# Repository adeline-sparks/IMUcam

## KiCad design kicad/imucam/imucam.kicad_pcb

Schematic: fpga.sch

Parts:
C1, C3, C5, C6, C7, C10, C11, C13, C16, C18, C20, C23, C25, C26, C27, C28, C29, C30, C31, C32, C33, C35, C37: 100nF; C_0402_1005Metric
C2, C8, C36: 1uF; C_0402_1005Metric
C4: 2.2uF; C_0402_1005Metric
C9, C12, C14, C15, C17, C19, C21, C22, C24, C34: 10uF; C_0603_1608Metric
D1: D_Schottky; D_0402_1005Metric
DONE1: RED; LED_0805_2012Metric
FB1, FB2, FB3, FB4, FB5: 120; L_0402_1005Metric
FPGA_LED1, FPGA_LED2, FPGA_LED3: RED; LED_0805_2012Metric
J1: JTAG; PinHeader_2x05_P1.27mm_Vertical
Q1, Q2, Q3, Q4: BSS214NW; SOT-323_SC-70
R1, R3, R5, R8, R11, R15: 10k; R_0402_1005Metric
R2, R4, R6, R9: 100; R_0402_1005Metric
R7, R12: 1k; R_0402_1005Metric
R10, R13, R14: 4.7k; R_0402_1005Metric
R16: 2.2k; R_0402_1005Metric
U1: TLV73310PDBVT; SOT-23-5
U2: LIFCL-17-xSG72; QFN-72-1EP_10x10mm_P0.5mm_EP6x6mm
U3: AT25SF081-SSHD-X; SOIC-8_3.9x4.9mm_P1.27mm
X1: ECS-2520MV-xxx-xx; Oscillator_SMD_ECS_2520MV-xxx-xx-4Pin_2.5x2.0mm

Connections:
+1V0: C1.1, C3.1, C5.1, C7.1, C8.1, C10.1, C12.1, C13.1, C17.1, C18.1, C24.1, C25.1, FB1.1, FB3.1, U1.5, U2.5 (VCC), U2.6 (VCC), U2.12 (VCC), U2.21 (VCC), U2.35 (VCC), U2.38 (VCC), U2.40 (VCC), U2.62 (VCC)
/FPGA/1V0A_PHY: C15.1, C16.1, C23.1, FB3.2, U2.70 (VCCDPHY0), U2.72 (VCCDPHY0)
/FPGA/1V0A_PLL: C4.1, C6.1, FB1.2, U2.63 (VCCPLLDPHY0)
/FPGA/1V8A: C30.1, C31.1, C32.1, C33.1, C34.1, FB4.2, U2.7 (VCCAUX), U2.17 (VCCAUXH5), U2.29 (VCCAUXH3), U2.47 (VCCAUX)
/FPGA/1V8A_PHY: C9.1, C11.1, FB2.2, U2.71 (VCCADPHY0)
/FPGA/FLASH_CS: R11.2, U2.56 (PT61A/MCSN), U3.1
/FPGA/FLASH_SCK: R12.1, U2.59 (PT59A/MCLK), U3.6
/FPGA/FLASH_SI: U2.57 (PT61B/MOSI), U3.5
/FPGA/FLASH_SO: U2.51 (PT63A/MISO), U3.2
/FPGA/JTAG_RESET: D1.2, J1.10, R15.2, U2.60 (PT57B/PROGRAMN)
/FPGA/JTAG_TCK: J1.4, R16.1, U2.41 (PR9A/TCK)
/FPGA/JTAG_TDI: J1.8, R10.2, U2.46 (PR5A/TDI)
/FPGA/JTAG_TDO: J1.6, R13.2, U2.45 (PR5B/TDO)
/FPGA/JTAG_TMS: J1.2, R14.2, U2.48 (PR3B/TMS)
/FPGA/LED1: Q1.1, R1.1, U2.9 (PB30A)
/FPGA/LED2: Q2.1, R3.1, U2.8 (PB30B)
/FPGA/LED3: Q3.1, R5.1, U2.37 (PB70B)
CAM_SLVS0_N: U2.34 (PB68B); also elsewhere on the board
CAM_SLVS0_P: U2.33 (PB68A); also elsewhere on the board
CAM_SLVS1_N: U2.31 (PB66B); also elsewhere on the board
CAM_SLVS1_P: U2.30 (PB66A); also elsewhere on the board
CAM_SLVS2_N: U2.25 (PB60B); also elsewhere on the board
CAM_SLVS2_P: U2.24 (PB60A); also elsewhere on the board
CAM_SLVS3_N: U2.23 (PB56B); also elsewhere on the board
CAM_SLVS3_P: U2.22 (PB56A); also elsewhere on the board
CAM_SLVSC_N: U2.28 (PB64B); also elsewhere on the board
CAM_SLVSC_P: U2.27 (PB64A); also elsewhere on the board
CLK_24MHZ: U2.36 (PB70A), X1.3; also elsewhere on the board
EXTCAM_CLK_N: U2.69 (DPHY0_CKN); also elsewhere on the board
EXTCAM_CLK_P: U2.68 (DPHY0_CKP); also elsewhere on the board
EXTCAM_D0_N: U2.3 (DPHY0_DN0); also elsewhere on the board
EXTCAM_D0_P: U2.4 (DPHY0_DP0); also elsewhere on the board
EXTCAM_D1_N: U2.67 (DPHY0_DN1); also elsewhere on the board
EXTCAM_D1_P: U2.66 (DPHY0_DP1); also elsewhere on the board
EXTCAM_D2_N: U2.2 (DPHY0_DN2); also elsewhere on the board
EXTCAM_D2_P: U2.1 (DPHY0_DP2); also elsewhere on the board
EXTCAM_D3_N: U2.65 (DPHY0_DN3); also elsewhere on the board
EXTCAM_D3_P: U2.64 (DPHY0_DP3); also elsewhere on the board
FPGA_CS: U2.61 (PT57A/INITN); also elsewhere on the board
FPGA_DONE: Q4.1, R8.2, U2.58 (PT59B/DONE); also elsewhere on the board
FPGA_INT: U2.43 (PR9B); also elsewhere on the board
FPGA_SCK: U2.55 (PT63B); also elsewhere on the board
FPGA_SI: U2.52 (PT65A); also elsewhere on the board
FPGA_SO: U2.53 (PT65B); also elsewhere on the board
HDMI_CK_N: U2.20 (PB26B); also elsewhere on the board
HDMI_CK_P: U2.19 (PB26A); also elsewhere on the board
HDMI_D0_N: U2.16 (PB18A); also elsewhere on the board
HDMI_D0_P: U2.15 (PB18B); also elsewhere on the board
HDMI_D1_N: U2.14 (PB16A); also elsewhere on the board
HDMI_D1_P: U2.13 (PB16B); also elsewhere on the board
HDMI_D2_N: U2.11 (PB20A); also elsewhere on the board
HDMI_D2_P: U2.10 (PB20B); also elsewhere on the board
NRST: D1.1; also elsewhere on the board
unnamed: C36.1, C37.1, FB5.2, X1.4
unnamed: DONE1.1, Q4.3
unnamed: DONE1.2, R9.2
unnamed: FPGA_LED1.1, Q1.3
unnamed: FPGA_LED1.2, R2.2
unnamed: FPGA_LED2.1, Q2.3
unnamed: FPGA_LED2.2, R4.2
unnamed: FPGA_LED3.1, Q3.3
unnamed: FPGA_LED3.2, R6.2
unnamed: R7.2, U2.50 (JTAG_EN)
SCL_3V3: U2.44 (PR7B/SCL); also elsewhere on the board
SDA_3V3: U2.42 (PR7A/SDA); also elsewhere on the board

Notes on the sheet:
Data pairs are swapped

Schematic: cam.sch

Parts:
C38, C39, C40, C41, C44, C45, C48, C50: 1uF; C_0402_1005Metric
C42, C43, C46, C47, C49, C51: 100nF; C_0402_1005Metric
H1: M12Lens; M12_Lens_20mm
H2: EXTCAM; Arducam_module_40mm
J2: EXTCAM; Molex_545482271
R17: 4.7k; R_0402_1005Metric
U4: MIC5365-2.8YD5; SOT-23-5
U5: AR0330CM1C00; CLCC48

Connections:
+2V8: C39.1, C41.1, C43.1, C45.1, C47.1, C48.1, C49.1, C50.1, C51.1, U4.5, U5.17 (VDD_PLL), U5.23 (VDD_HISPI_TX), U5.40 (VAA), U5.42 (VAA_PIX)
CAM_RESET_BAR: R17.2, U5.37 (RESET_BAR); also elsewhere on the board
CAM_SLVS0_N: U5.19 (SLVLS0_N); also elsewhere on the board
CAM_SLVS0_P: U5.20 (SLVLS0_P); also elsewhere on the board
CAM_SLVS1_N: U5.21 (SLVLS1_N); also elsewhere on the board
CAM_SLVS1_P: U5.22 (SLVLS1_P); also elsewhere on the board
CAM_SLVS2_N: U5.27 (SLVS2_N); also elsewhere on the board
CAM_SLVS2_P: U5.28 (SLVS2_P); also elsewhere on the board
CAM_SLVS3_N: U5.29 (SLVS3_N); also elsewhere on the board
CAM_SLVS3_P: U5.30 (SLVS3_P); also elsewhere on the board
CAM_SLVSC_N: U5.25 (SLVSC_N); also elsewhere on the board
CAM_SLVSC_P: U5.26 (SLVSC_P); also elsewhere on the board
CAM_TRIGGER: U5.36 (TRIGGER); also elsewhere on the board
CLK_24MHZ: U5.38 (EXTCLK); also elsewhere on the board
EXTCAM_CLK_N: J2.8; also elsewhere on the board
EXTCAM_CLK_P: J2.9; also elsewhere on the board
EXTCAM_D0_N: J2.2; also elsewhere on the board
EXTCAM_D0_P: J2.3; also elsewhere on the board
EXTCAM_D1_N: J2.5; also elsewhere on the board
EXTCAM_D1_P: J2.6; also elsewhere on the board
EXTCAM_D2_N: J2.11; also elsewhere on the board
EXTCAM_D2_P: J2.12; also elsewhere on the board
EXTCAM_D3_N: J2.14; also elsewhere on the board
EXTCAM_D3_P: J2.15; also elsewhere on the board
EXTCAM_IO0: J2.17; also elsewhere on the board
EXTCAM_IO1: J2.18; also elsewhere on the board
SCL_1V8: U5.1 (S_CLK); also elsewhere on the board
SCL_3V3: J2.20; also elsewhere on the board
SDA_1V8: U5.2 (S_DATA); also elsewhere on the board
SDA_3V3: J2.21; also elsewhere on the board

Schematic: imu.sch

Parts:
C52, C53, C54: 100nF; C_0402_1005Metric
U6: ICM20948; QFN-24-1EP_3x3mm_P0.4mm_EP1.75x1.6mm_NoDiePad

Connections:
CAM_TRIGGER: U6.11 (FSYNC); also elsewhere on the board
IMU_CS: U6.22 (nCS); also elsewhere on the board
IMU_INT: U6.12 (INT1); also elsewhere on the board
IMU_SCK: U6.23 (SCL/SCLK); also elsewhere on the board
IMU_SI: U6.24 (SDA/SDI); also elsewhere on the board
IMU_SO: U6.9 (SDO/AD0); also elsewhere on the board
unnamed: C54.1, U6.10 (REGOUT)
SCL_1V8: U6.7 (AUX_CL); also elsewhere on the board
SDA_1V8: U6.21 (AUX_DA); also elsewhere on the board

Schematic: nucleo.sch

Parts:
C55, C60: 10uF; C_0603_1608Metric
C56, C57, C58, C61, C62, C63, C65: 100nF; C_0402_1005Metric
C59, C64: 22uF; C_0603_1608Metric
J3: NUCLEO_CN8; PinHeader_2x08_P2.54mm_Vertical
J4: NUCLEO_CN9; PinHeader_2x15_P2.54mm_Vertical
J5: NUCLEO_CN7; PinHeader_2x10_P2.54mm_Vertical
J6: NUCLEO_CN10; PinHeader_2x17_P2.54mm_Vertical
L1, L2: 3.3uH; L_Coilcraft_XxL4020
PWR1: RED; LED_0805_2012Metric
R18: .05; R_0805_2012Metric
R19: 12.4k; R_0402_1005Metric
R20, R28: 10k; R_0402_1005Metric
R21, R22, R23, R24: 100; R_0402_1005Metric
R25, R26, R29, R30: 4.7k; R_0402_1005Metric
R27: 30.9k; R_0402_1005Metric
STM_LED1, STM_LED2, STM_LED3: RED; LED_0805_2012Metric
U7, U9: TPS562200; SOT-23-6
U8: INA219AxDCN; SOT-23-8
U10: NTS0308E; TSSOP-20_4.4x6.5mm_P0.65mm

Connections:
+5V: C55.1, C56.1, C60.1, C61.1, R18.2, U7.3, U7.5, U8.2, U9.3, U9.5; also elsewhere on the board
/nucleo/5V_IN: J3.9, R18.1, U8.1
/nucleo/CAM_TRIGGER_3V3: J6.10, U10.12
/nucleo/IMU_CS_3V3: J4.16, U10.14
/nucleo/IMU_INT_3V3: J4.22, U10.17
/nucleo/IMU_SCK_3V3: J4.14, U10.13
/nucleo/IMU_SI_3V3: J4.20, U10.16
/nucleo/IMU_SO_3V3: J4.18, U10.15
/nucleo/LED1: J3.6, R21.1
/nucleo/LED2: J3.8, R22.1
/nucleo/LED3: J3.10, R23.1
CAM_RESET_BAR: J6.2; also elsewhere on the board
CAM_TRIGGER: U10.9; also elsewhere on the board
EXTCAM_IO0: J6.4; also elsewhere on the board
EXTCAM_IO1: J6.6; also elsewhere on the board
FPGA_CS: J5.16; also elsewhere on the board
FPGA_DONE: J5.20; also elsewhere on the board
FPGA_INT: J5.18; also elsewhere on the board
FPGA_SCK: J5.10; also elsewhere on the board
FPGA_SI: J5.14; also elsewhere on the board
FPGA_SO: J5.12; also elsewhere on the board
HDMI_DDC_EN: J6.21; also elsewhere on the board
HDMI_EQ0: J6.13; also elsewhere on the board
HDMI_EQ1: J6.15; also elsewhere on the board
HDMI_HPD: J6.19; also elsewhere on the board
HDMI_OE: J6.23; also elsewhere on the board
HDMI_SCL: J6.8; also elsewhere on the board
HDMI_SDA: J6.12; also elsewhere on the board
IMU_CS: U10.7; also elsewhere on the board
IMU_INT: U10.4; also elsewhere on the board
IMU_SCK: U10.8; also elsewhere on the board
IMU_SI: U10.5; also elsewhere on the board
IMU_SO: U10.6; also elsewhere on the board
NRST: J3.5; also elsewhere on the board
unnamed: C57.1, L1.2, U7.2
unnamed: C57.2, U7.6
unnamed: C63.1, L2.2, U9.2
unnamed: C63.2, U9.6
unnamed: PWR1.2, R24.2
unnamed: R19.2, R20.1, U7.4
unnamed: R21.2, STM_LED1.2
unnamed: R22.2, STM_LED2.2
unnamed: R23.2, STM_LED3.2
unnamed: R27.2, R28.1, U9.4
SCL_1V8: R25.1, U10.3; also elsewhere on the board
SCL_3V3: J4.19, R30.2, U8.5, U10.18; also elsewhere on the board
SDA_1V8: R26.1, U10.1; also elsewhere on the board
SDA_3V3: J4.21, R29.2, U8.6, U10.20; also elsewhere on the board

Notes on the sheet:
EXTI15
Open Drain
EXTI3

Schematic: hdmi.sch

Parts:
C66, C67, C68, C69, C70, C71, C72, C73, C75, C76, C77: 100nF; C_0402_1005Metric
C74: 10uF; C_0603_1608Metric
J7: HDMI; CnC_2000-1-2-41-00-BK
R31, R32, R38, R39: 4.7k; R_0402_1005Metric
R33, R34, R35, R36: 10k; R_0402_1005Metric
R37: 12.4k 1%; R_0402_1005Metric
U11: PTN3366; QFN-32-1EP_5x5mm_P0.5mm_EP3.6x3.6mm
U12: AP2331; SOT-23

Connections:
+5V: C76.1, U12.3; also elsewhere on the board
/hdmi/5V_HDMI: C77.1, J7.18, R38.1, R39.1, U12.2
/hdmi/CK_N: J7.12, U11.10 (OUT_D4-)
/hdmi/CK_P: J7.10, U11.9 (OUT_D4+)
/hdmi/D0_N: J7.9, U11.12 (OUT_D3-)
/hdmi/D0_P: J7.7, U11.11 (OUT_D3+)
/hdmi/D1_N: J7.6, U11.14 (OUT_D2-)
/hdmi/D1_P: J7.4, U11.13 (OUT_D2+)
/hdmi/D2_N: J7.3, U11.16 (OUT_D1-)
/hdmi/D2_P: J7.1, U11.15 (OUT_D1+)
/hdmi/IN_D1+: C66.1, U11.26 (IN_D1+)
/hdmi/IN_D1-: C70.1, U11.25 (IN_D1-)
/hdmi/IN_D2+: C67.1, U11.28 (IN_D2+)
/hdmi/IN_D2-: C71.1, U11.27 (IN_D2-)
/hdmi/IN_D3+: C68.1, U11.30 (IN_D3+)
/hdmi/IN_D3-: C72.1, U11.29 (IN_D3-)
/hdmi/IN_D4+: C69.1, U11.32 (IN_D4+)
/hdmi/IN_D4-: C73.1, U11.31 (IN_D4-)
HDMI_CK_N: C70.2; also elsewhere on the board
HDMI_CK_P: C66.2; also elsewhere on the board
HDMI_D0_N: C71.2; also elsewhere on the board
HDMI_D0_P: C67.2; also elsewhere on the board
HDMI_D1_N: C72.2; also elsewhere on the board
HDMI_D1_P: C68.2; also elsewhere on the board
HDMI_D2_N: C73.2; also elsewhere on the board
HDMI_D2_P: C69.2; also elsewhere on the board
HDMI_DDC_EN: R34.2, U11.22 (DDC_EN); also elsewhere on the board
HDMI_EQ0: R35.2, U11.8 (EQ0); also elsewhere on the board
HDMI_EQ1: R36.2, U11.2 (EQ1); also elsewhere on the board
HDMI_HPD: U11.5 (HPD_SOURCE); also elsewhere on the board
HDMI_OE: R33.1, U11.17 (OE_N); also elsewhere on the board
HDMI_SCL: R31.2, U11.7 (SCL_SOURCE); also elsewhere on the board
HDMI_SDA: R32.2, U11.6 (SDA_SOURCE); also elsewhere on the board
unnamed: J7.15, R38.2, U11.19 (SCL_SINK)
unnamed: J7.16, R39.2, U11.20 (SDA_SINK)
unnamed: J7.19, U11.21 (HPD_SINK)
unnamed: R37.1, U11.4 (REXT)

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
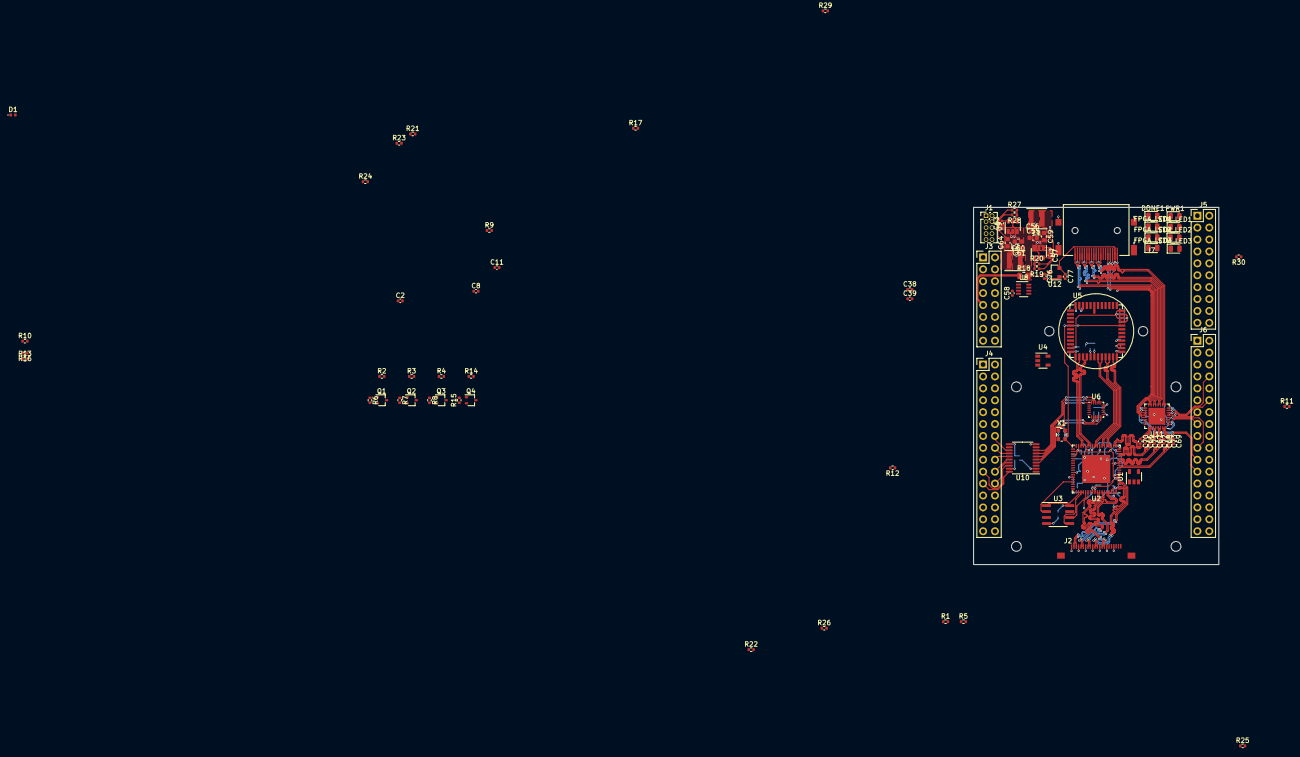
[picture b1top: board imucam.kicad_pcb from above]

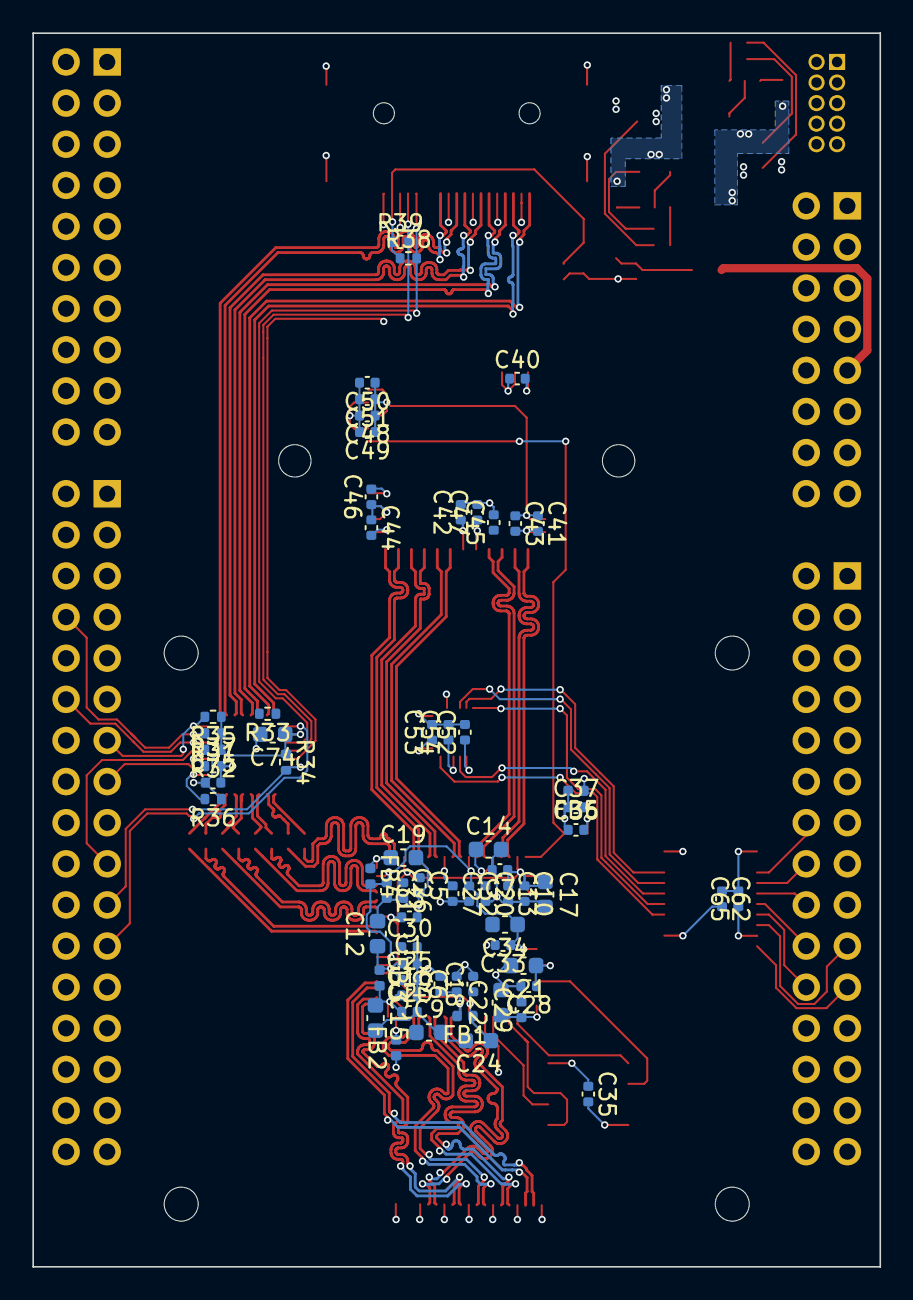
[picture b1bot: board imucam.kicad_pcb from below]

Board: 4 copper layers, 52.3 x 76.2 mm, 158 parts (67 on the bottom side), 130 nets.

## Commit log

2021-04-24 Adding datasheets
2021-04-24 Switching to Cyclone 10 LP
2021-04-24 Initial quartus project
2021-04-24 Implemented summation_tree
2021-04-24 Renamed to adder_tree
2021-04-24 Added valid signals
2021-04-24 Found paper on boxplus manifolds
2021-04-24 Added EKF paper
2021-04-25 Renamed std_logic_vector array types
2021-04-25 Enabled ModelSim-Altera in quartus project
2021-04-25 Just make the adder tree always signed.
2021-04-25 Initial sobel implementation
2021-04-25 Remove registers on sign extension/shifting
2021-04-25 Rename sobel to sobel_kernel
2021-04-25 Implemented harris tensor
2021-04-25 Round at the end of adder_tree
2021-04-25 Made rounding into a registered entity
2021-04-25 Added camera datasheets
2021-04-26 Added D-PHY emulation application note
2021-04-26 More FPGA datasheets
2021-04-26 Reorganized datasheets and found a new part
2021-04-27 Pivot! Going to give BGA a shot with ZYNQ-7000
2021-04-27 Zynq datasheets
2021-04-27 FPGA datasheets
2021-04-27 Created vivado project
2021-04-27 Moar docs
2021-05-01 Coded initial version of HiSpi receiver
2021-05-05 Swapped to AR0330 again for hand soldering
2021-05-05 Pivoting back to Cyclone 10 LP for hand soldering
2021-05-06 Prototyped window buffer
2021-05-08 Got rid of implicit port sizes
2021-06-01 Created kicad for cyclone 10 LP but might go back to crosslink-nx
2021-06-11 Added more footprints
2021-06-18 Went ham on schematic
2021-06-18 Cleaned up footprints
2021-06-19 All components have footprints!
2021-06-19 Annotated schematic
2021-06-25 Final schematic rev?
2021-07-10 Lots of schematic work
2021-07-10 vhdl work
2021-07-21 Added 3.3v power LED
2021-09-08 Remove colons from PDF file names
2021-09-08 Cleaned out defunct project
2021-09-08 More work on PCB
2021-09-09 Switched FSYNC to use TRIGGER, lots of PCB work
2021-09-09 Through-hole JTAG
2021-09-10 More PCB work, began current sense
2021-09-10 Slightly more progress on current measurement
2021-09-11 Turns out, we need level translators
2021-09-12 WIP of remapping nucleo pinout for pcb routing
2021-09-12 Ready to begin routing differential pairs
2021-09-13 Routed first differential pairs
2021-09-15 More routing
